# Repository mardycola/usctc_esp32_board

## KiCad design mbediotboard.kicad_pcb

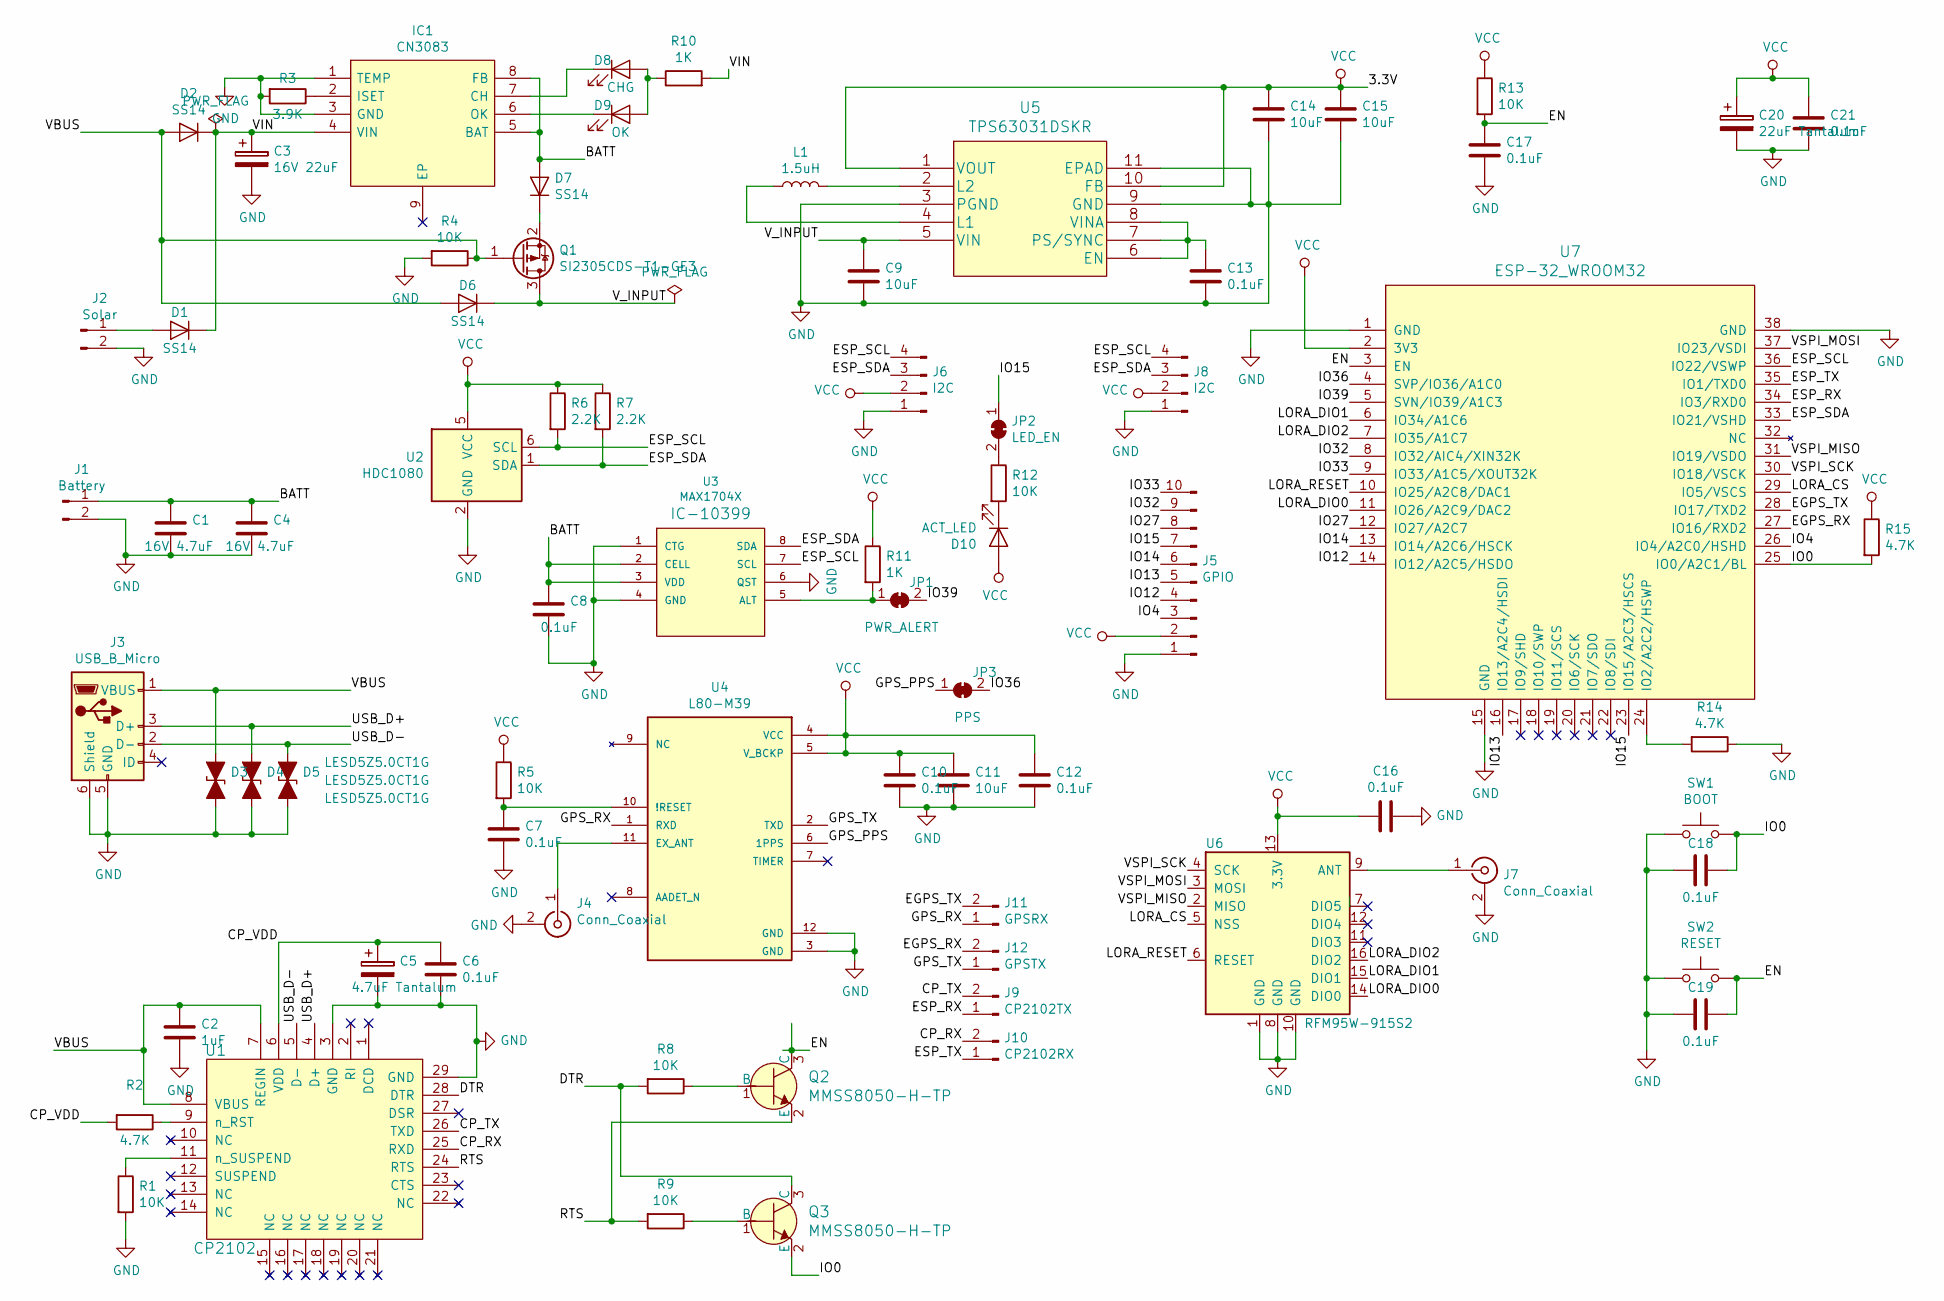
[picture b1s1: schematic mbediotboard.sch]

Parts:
C1, C4: 16V 4.7uF; C_0805_2012Metric_Pad1.15x1.40mm_HandSolder
C2: 1uF; C_0805_2012Metric_Pad1.15x1.40mm_HandSolder
C3: 16V 22uF; CP_EIA-3216-18_Kemet-A_Pad1.58x1.35mm_HandSolder
C5: 4.7uF Tantalum; CP_EIA-3216-18_Kemet-A_Pad1.58x1.35mm_HandSolder
C6, C7, C8, C10, C12, C13, C16, C18, C19, C21: 0.1uF; C_0805_2012Metric_Pad1.15x1.40mm_HandSolder
C9, C11, C14, C15: 10uF; C_0805_2012Metric_Pad1.15x1.40mm_HandSolder
C17: 0.1uF; C_1206_3216Metric_Pad1.42x1.75mm_HandSolder
C20: 22uF Tantalum; CP_EIA-3216-18_Kemet-A_Pad1.58x1.35mm_HandSolder
D1, D2, D6, D7: SS14; D_SMA_Handsoldering
D3, D4, D5: LESD5Z5.0CT1G; D_SOD-523
D8: CHG; LED_0805_2012Metric_Pad1.15x1.40mm_HandSolder
D9: OK; LED_0805_2012Metric_Pad1.15x1.40mm_HandSolder
D10: ACT_LED; LED_0805_2012Metric_Pad1.15x1.40mm_HandSolder
IC1: CN3083; SOIC-8-1EP_3.9x4.9mm_P1.27mm_EP2.35x2.35mm; Manufacturer_Part_Number CN3083
J1: Battery; Molex_PicoBlade_53261-0271_1x02-1MP_P1.25mm_Horizontal
J2: Solar; Molex_PicoBlade_53261-0271_1x02-1MP_P1.25mm_Horizontal
J3: USB_B_Micro; USB_Micro-B_Molex_47346-0001
J4, J7: Conn_Coaxial; U.FL_Hirose_U.FL-R-SMT-1_Vertical
J5: GPIO; JST_PH_S10B-PH-K_1x10_P2.00mm_Horizontal
J6, J8: I2C; JST_PH_S4B-PH-K_1x04_P2.00mm_Horizontal
J9: CP2102TX; PinHeader_1x02_P2.00mm_Vertical
J10: CP2102RX; PinHeader_1x02_P2.00mm_Vertical
J11: GPSRX; PinHeader_1x02_P2.00mm_Vertical
J12: GPSTX; PinHeader_1x02_P2.00mm_Vertical
JP1: PWR_ALERT; SolderJumper-2_P1.3mm_Bridged_RoundedPad1.0x1.5mm
JP2: LED_EN; SolderJumper-2_P1.3mm_Bridged_RoundedPad1.0x1.5mm
JP3: PPS; SolderJumper-2_P1.3mm_Bridged_RoundedPad1.0x1.5mm
L1: 1.5uH; L_0805_2012Metric_Pad1.15x1.40mm_HandSolder
Q1: SI2305CDS-T1-GE3; SOT-23
Q2, Q3: MMSS8050-H-TP; SOT-23-3; MPN MMSS8050-H-TP; Digi-Key_PN MMSS8050-H-TPMSCT-ND
R1, R4, R5, R8, R9, R12, R13: 10K; R_0805_2012Metric_Pad1.15x1.40mm_HandSolder
R2, R14, R15: 4.7K; R_0805_2012Metric_Pad1.15x1.40mm_HandSolder
R3: 3.9K; R_0805_2012Metric_Pad1.15x1.40mm_HandSolder
R6, R7: 2.2K; R_0805_2012Metric_Pad1.15x1.40mm_HandSolder
R10, R11: 1K; R_0805_2012Metric_Pad1.15x1.40mm_HandSolder
SW1: BOOT; SW_PUSH_6mm_H4.3mm
SW2: RESET; SW_PUSH_6mm_H4.3mm
U1: CP2102; QFN-28-1EP_5x5mm_P0.5mm_EP3.35x3.35mm
U2: HDC1080; Texas_PWSON-N6
U3: MAX1704X; TDFN-8-1EP_3x2mm_P0.5mm_EP1.80x1.65mm
U4: L80-M39; QUECTEL_L80-M39
U5: TPS63031DSKR; VSON-10-1EP_3x3mm_P0.5mm_EP1.2x2mm_ThermalVias
U6: RFM95W-915S2; HOPERF_RFM9XW_SMD
U7: ESP-32_WROOM32; ESP32-WROOM-32

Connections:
/BATT: C1.1, C4.1, C8.1, D7.2 (A), IC1.5 (BAT), IC1.8 (FB), J1.1, U3.2 (CELL), U3.3 (VDD)
/CP_RX: J10.2, U1.25 (RXD)
/CP_TX: J9.2, U1.26 (TXD)
/CP_VDD: C5.1, C6.1, R2.2, U1.6 (VDD)
/DTR: Q3.3 (C), R8.2, U1.28 (DTR)
/EGPS_RX: J12.2, U7.27 (IO16/RXD2)
/EGPS_TX: J11.2, U7.28 (IO17/TXD2)
/EN: C17.1, C19.2, Q2.3 (C), R13.2, SW2.2, U7.3 (EN)
/ESP_RX: J9.1, U7.34 (IO3/RXD0)
/ESP_SCL: J6.4, J8.4, R6.2, U2.6 (SCL), U3.7 (SCL), U7.36 (IO22/VSWP)
/ESP_SDA: J6.3, J8.3, R7.2, U2.1 (SDA), U3.8 (SDA), U7.33 (IO21/VSHD)
/ESP_TX: J10.1, U7.35 (IO1/TXD0)
/GPS_PPS: JP3.1 (A), U4.6 (1PPS)
/GPS_RX: J11.1, U4.1 (RXD)
/GPS_TX: J12.1, U4.2 (TXD)
/IO0: C18.2, Q3.2 (E), R15.2, SW1.2, U7.25 (IO0/A2C1/BL)
/IO4: J5.3, U7.26 (IO4/A2C0/HSHD)
/IO12: J5.4, U7.14 (IO12/A2C5/HSDO)
/IO13: J5.5, U7.16 (IO13/A2C4/HSDI)
/IO14: J5.6, U7.13 (IO14/A2C6/HSCK)
/IO15: J5.7, JP2.1 (A), U7.23 (IO15/A2C3/HSCS)
/IO27: J5.8, U7.12 (IO27/A2C7)
/IO32: J5.9, U7.8 (IO32/AIC4/XIN32K)
/IO33: J5.10, U7.9 (IO33/A1C5/XOUT32K)
/IO36: JP3.2 (B), U7.4 (SVP/IO36/A1C0)
/IO39: JP1.2 (B), U7.5 (SVN/IO39/A1C3)
/LORA_CS: U6.5 (NSS), U7.29 (IO5/VSCS)
/LORA_DIO0: U6.14 (DIO0), U7.11 (IO26/A2C9/DAC2)
/LORA_DIO1: U6.15 (DIO1), U7.6 (IO34/A1C6)
/LORA_DIO2: U6.16 (DIO2), U7.7 (IO35/A1C7)
/LORA_RESET: U6.6 (RESET), U7.10 (IO25/A2C8/DAC1)
/RTS: Q2.2 (E), R9.2, U1.24 (RTS)
/USB_D+: D4.1 (A1), J3.3 (D+), U1.4 (D+)
/USB_D-: D5.1 (A1), J3.2 (D-), U1.5 (D-)
/VBUS: C2.1, D2.2 (A), D3.1 (A1), D6.2 (A), J3.1 (VBUS), Q1.1 (G), R4.1, U1.7 (REGIN), U1.8 (VBUS)
/VIN: C3.1, D1.1 (K), D2.1 (K), IC1.4 (VIN), R10.2
/VSPI_MISO: U6.2 (MISO), U7.31 (IO19/VSDO)
/VSPI_MOSI: U6.3 (MOSI), U7.37 (IO23/VSDI)
/VSPI_SCK: U6.4 (SCK), U7.30 (IO18/VSCK)
/V_INPUT: C9.1, D6.1 (K), Q1.3 (D), U5.5 (VIN)
GND: C1.2, C2.2, C3.2, C4.2, C5.2, C6.2, C7.2, C8.2, C9.2, C10.2, C11.2, C12.2, C13.2, C14.2, C15.2, C16.1, C17.2, C18.1, C19.1, C20.2, C21.2, D3.2 (A2), D4.2 (A2), D5.2 (A2), IC1.1 (TEMP), IC1.3 (GND), J1.2, J2.2, J3.5 (GND), J3.6 (Shield), J4.2 (Ext), J5.1, J6.1, J7.2 (Ext), J8.1, R1.2, R3.2, R4.2, R14.1, SW1.1, SW2.1, U1.3 (GND), U1.29 (GND), U2.2 (GND), U2.7 (GND), U3.1 (CTG), U3.4 (GND), U3.6 (QST), U4.3 (GND), U4.12 (GND), U5.3 (PGND), U5.9 (GND), U5.11 (EPAD), U6.1 (GND), U6.8 (GND), U6.10 (GND), U7.1 (GND), U7.15 (GND), U7.38 (GND)
unnamed: C7.1, R5.2, U4.10 (!RESET)
unnamed: C13.1, U5.6 (EN), U5.7 (PS/SYNC), U5.8 (VINA)
unnamed: D1.2 (A), J2.1
unnamed: D7.1 (K), Q1.2 (S)
unnamed: D8.1 (K), IC1.7 (CH)
unnamed: D8.2 (A), D9.2 (A), R10.1
unnamed: D9.1 (K), IC1.6 (OK)
unnamed: D10.1 (K), R12.2
unnamed: IC1.2 (ISET), R3.1
unnamed: J4.1 (In), U4.11 (EX_ANT)
unnamed: J7.1 (In), U6.9 (ANT)
unnamed: JP1.1 (A), R11.2, U3.5 (ALT)
unnamed: JP2.2 (B), R12.1
unnamed: L1.1, U5.4 (L1)
unnamed: L1.2, U5.2 (L2)
unnamed: Q2.1 (B), R8.1
unnamed: Q3.1 (B), R9.1
unnamed: R1.1, U1.11 (n_SUSPEND)
unnamed: R2.1, U1.9 (n_RST)
unnamed: R14.2, U7.24 (IO2/A2C2/HSWP)
VCC: C10.1, C11.1, C12.1, C14.1, C15.1, C16.2, C20.1, C21.1, D10.2 (A), J5.2, J6.2, J8.2, R5.1, R6.1, R7.1, R11.1, R13.1, R15.1, U2.5 (VCC), U4.4 (VCC), U4.5 (V_BCKP), U5.1 (VOUT), U5.10 (FB), U6.13 (3.3V), U7.2 (3V3)

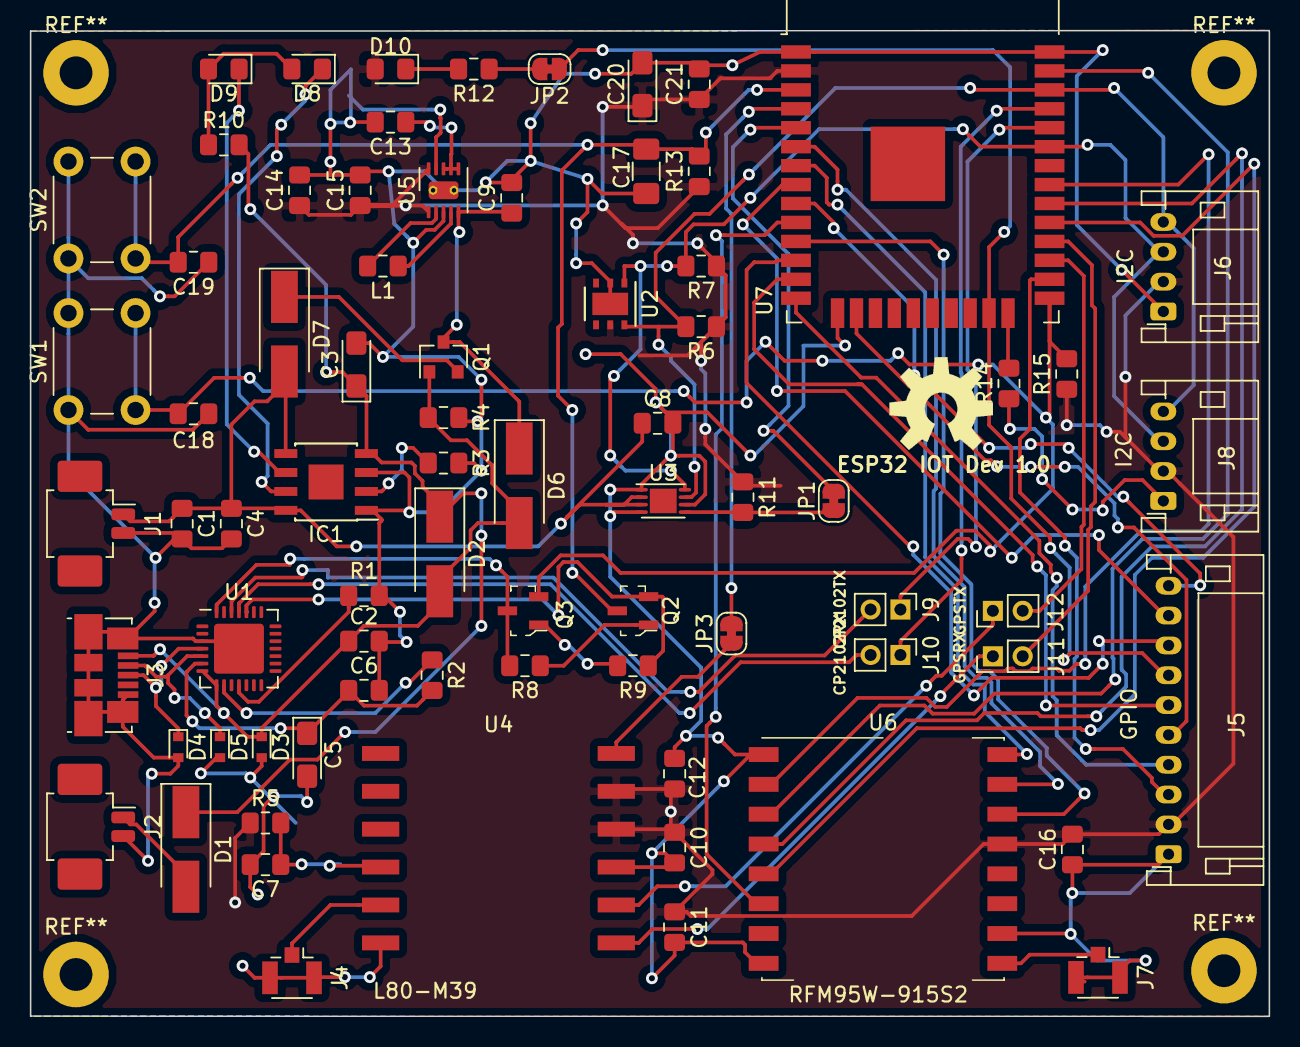
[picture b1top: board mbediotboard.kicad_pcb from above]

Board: 2 copper layers, 83.1 x 66.1 mm, 75 parts (0 on the bottom side), 62 nets.

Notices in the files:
mbediotboard.kicad_pcb:
© Cola,Cubero,Gaquit,Morala,Palugod
